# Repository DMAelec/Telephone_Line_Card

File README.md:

# Telephone Line Card

A twisted pair local loop interface for land line telephones. Performs similar functions to a telephone central office such as: loop battery feed, off-hook detection, ring voltage switching, and isolation to the voice line switching network.

Requires a 24-48VDC input to provide power to the phone and 90VAC for ringing the telephone bell. You can use a ringing generator module such as Cambridge Labs: Black Magic or a Power Dsine PCR-SIN03V12F20-C

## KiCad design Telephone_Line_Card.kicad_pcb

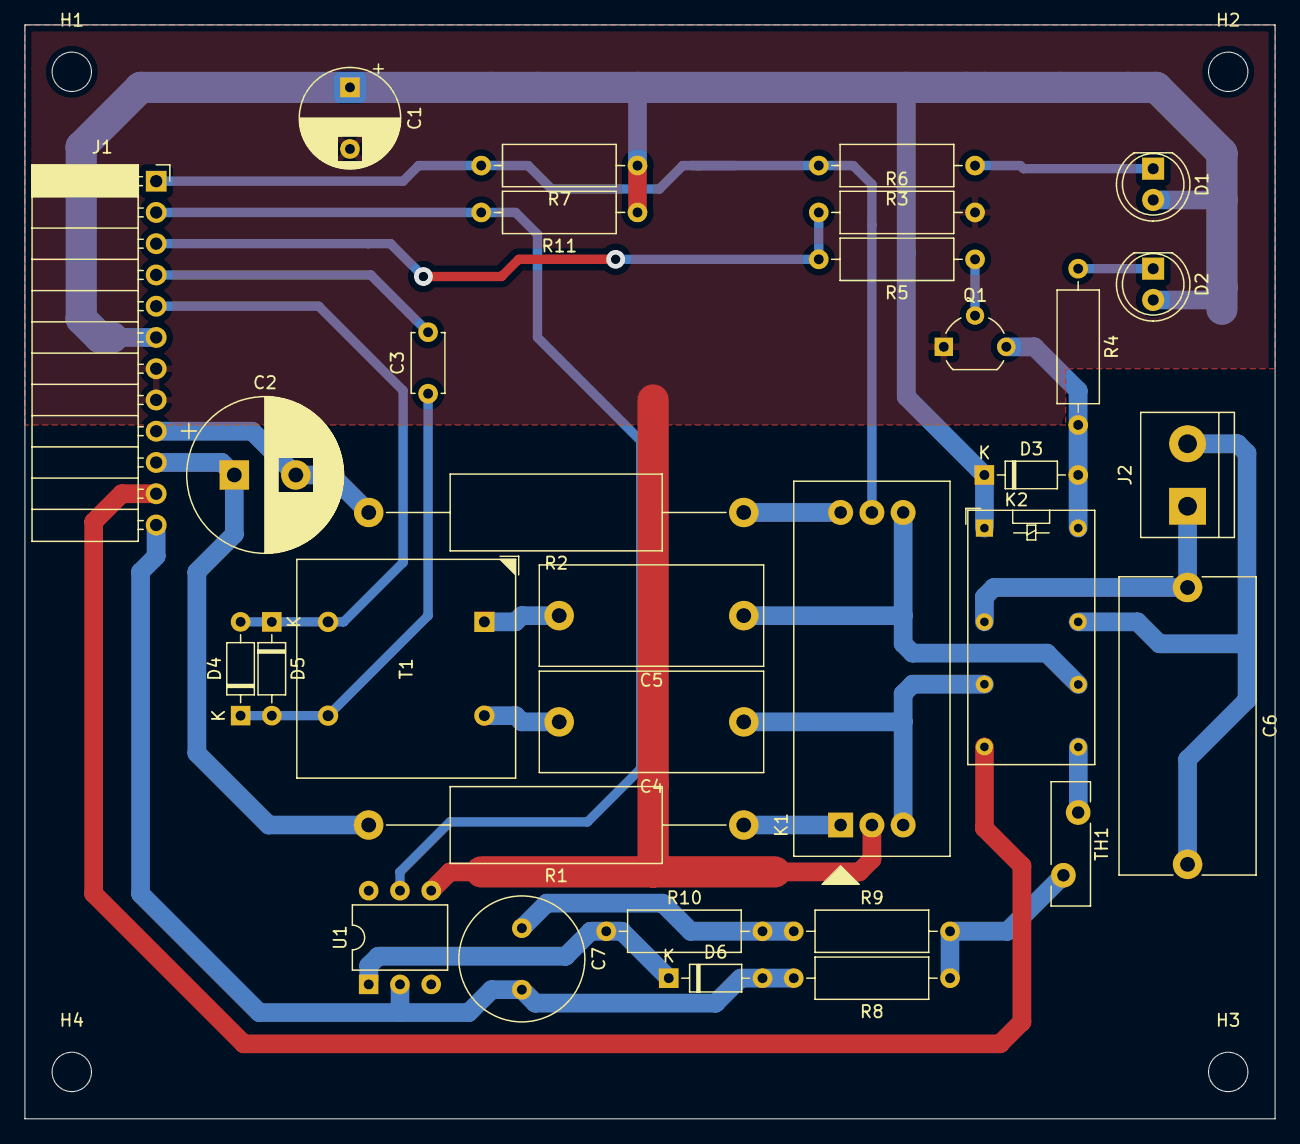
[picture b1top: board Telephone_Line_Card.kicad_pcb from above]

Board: 2 copper layers, 101.6 x 88.9 mm, 36 parts (0 on the bottom side), 28 nets.

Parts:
C1: 100uF; CP_Radial_D8.0mm_P5.00mm
C2: 100uF/100V; CP_Radial_D12.5mm_P5.00mm
C3: 0.1uF; C_Disc_D4.7mm_W2.5mm_P5.00mm
C4, C5: 2uF/100V; C_Rect_L18.0mm_W8.0mm_P15.00mm_FKS3_FKP3
C6: RC .1uF/47R; C_Rect_L24.0mm_W10.9mm_P22.50mm_MKT
C7: 47uF/10V; C_Radial_D10.0mm_H12.5mm_P5.00mm
D1: OFFHOOK_LED; LED_D5.0mm
D2: RING_LED; LED_D5.0mm
D3, D4, D5, D6: 1N4148; D_DO-35_SOD27_P7.62mm_Horizontal
H1, H2, H3, H4: MountingHole; MountingHole_3.2mm_M3
J1: Conn_01x12; PinSocket_1x12_P2.54mm_Horizontal
J2: RJ11; TerminalBlock_bornier-2_P5.08mm
K1: TELTONE_M949-1; Teltone_M-949-1
K2: G5V-2; Relay_DPDT_Omron_G5V-2
Q1: 2N3904; TO-92_Wide
R1, R2: 330R/2W; R_Axial_DIN0617_L17.0mm_D6.0mm_P30.48mm_Horizontal
R3, R4, R5: 1K; R_Axial_DIN0309_L9.0mm_D3.2mm_P12.70mm_Horizontal
R6, R7, R11: 10K; R_Axial_DIN0309_L9.0mm_D3.2mm_P12.70mm_Horizontal
R8: 620R; R_Axial_DIN0309_L9.0mm_D3.2mm_P12.70mm_Horizontal
R9, R10: 5K; R_Axial_DIN0309_L9.0mm_D3.2mm_P12.70mm_Horizontal
T1: 600:600; Transformer_Bourns_LM-NP-1001_1xSec
TH1: Thermistor_PTC; Fuse_Bourns_MF-RG400
U1: 4N35; DIP-6_W7.62mm

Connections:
+5V: C1.1, D1.2, D2.2, D3.1, J1.6, K2.1, R7.1, R11.1
-24V: C2.2, J1.9, R2.2
Earth: C2.1, J1.10, R1.2
GND: C1.2, J1.7, J1.8, K1.5, Q1.1, R6.2, U1.4
unnamed: C3.1, D4.1, D5.2, T1.5
unnamed: C4.1, K1.2, K2.6
unnamed: C4.2, T1.4
unnamed: C5.1, K1.3, K2.11
unnamed: C5.2, T1.1
unnamed: C6.1, J2.1, K2.4
unnamed: C6.2, J2.2, K2.13
unnamed: C7.1, R9.1, R10.2
unnamed: D1.1, R3.1
unnamed: D2.1, R4.1
unnamed: D3.2, K2.16, Q1.3, R4.2
unnamed: D6.1, R10.1, U1.1
unnamed: K1.1, R1.1
unnamed: K1.4, R2.1
unnamed: K2.9, TH1.1
unnamed: Q1.2, R5.1
unnamed: R8.1, R9.2, TH1.2
RING_BUS(R): C7.2, D6.2, J1.12, R8.2, U1.2
RING_BUS(T): J1.11, K2.8
RM: J1.3, R5.2, R6.1
RT: J1.2, R11.2, U1.5
SHK: J1.1, K1.6, R3.2, R7.2
VOICE_LINE(R): D4.2, D5.1, J1.5, T1.8
VOICE_LINE(T): C3.2, J1.4

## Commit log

2023-03-02 some schematic changes
2023-03-03 added slic sch symbol
2023-03-09 some changes
2023-03-09 some pcb changes
2023-03-12 some more pcb changes
2023-03-13 generated gerbers
2023-03-13 generated schematic pdf
2023-03-13 updated readme file
2023-03-13 readme file changes
